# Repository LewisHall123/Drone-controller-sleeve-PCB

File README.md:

# Drone-controller-sleeve-PCB
A circuit designed to send commands to a drone that it controls. The inputs to the circuit that determine the commands come from six separate tribo-electric nanogenerators (TENG). The materials used for the TENG were aluminium foil and fluorinated ethylene propylene (FEP). The aluminium foil was arranged as six squares that sat on a sleeve that was secured to the users forearm. The aluminium squares were connected to electrodes that were inputs to the circuit. A glove was used with FEP material on the fingertips, and so when the user touched the aluminium squares on the sleeve, a voltage was created in the aluminium squares.
The six aluminium squares were controlls that were responsible for increasing or decreasing the values of roll, pitch, and yaw of the drone.
A Raspberry Pi Pico was used to determine the exact messages that could be sent to the HC-12 transceiver that would transmitt the commands to the drone.

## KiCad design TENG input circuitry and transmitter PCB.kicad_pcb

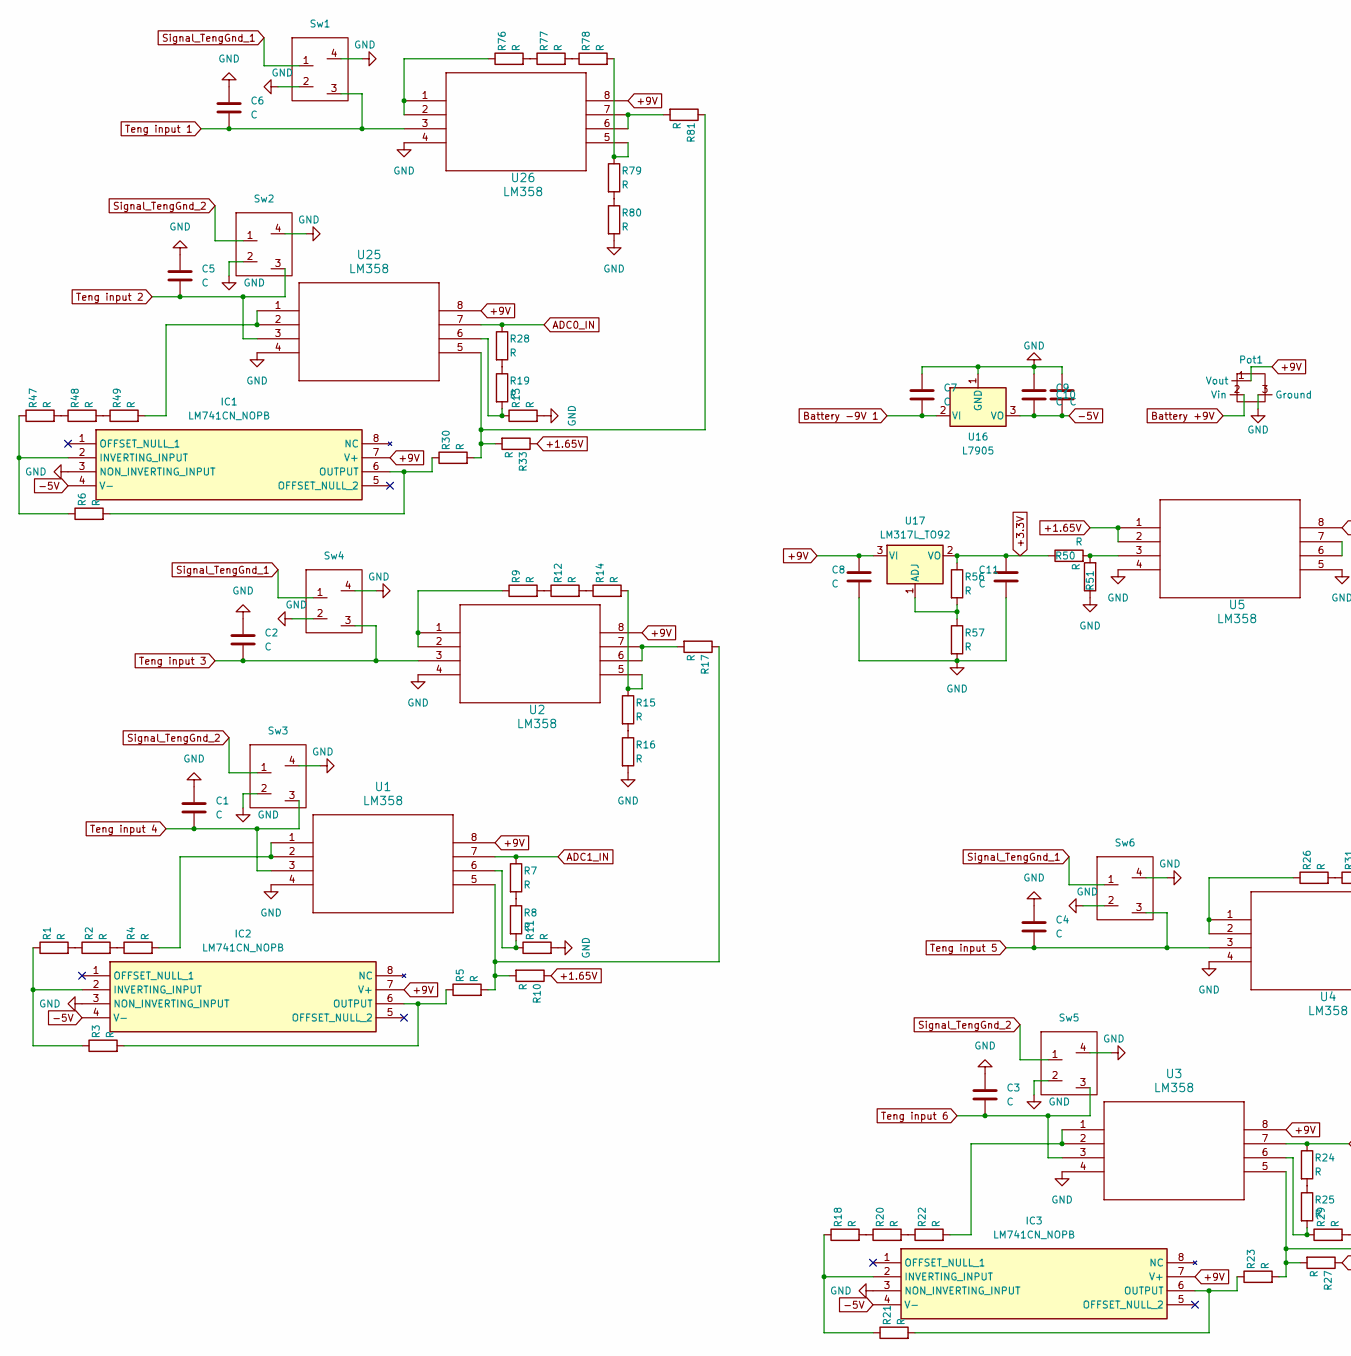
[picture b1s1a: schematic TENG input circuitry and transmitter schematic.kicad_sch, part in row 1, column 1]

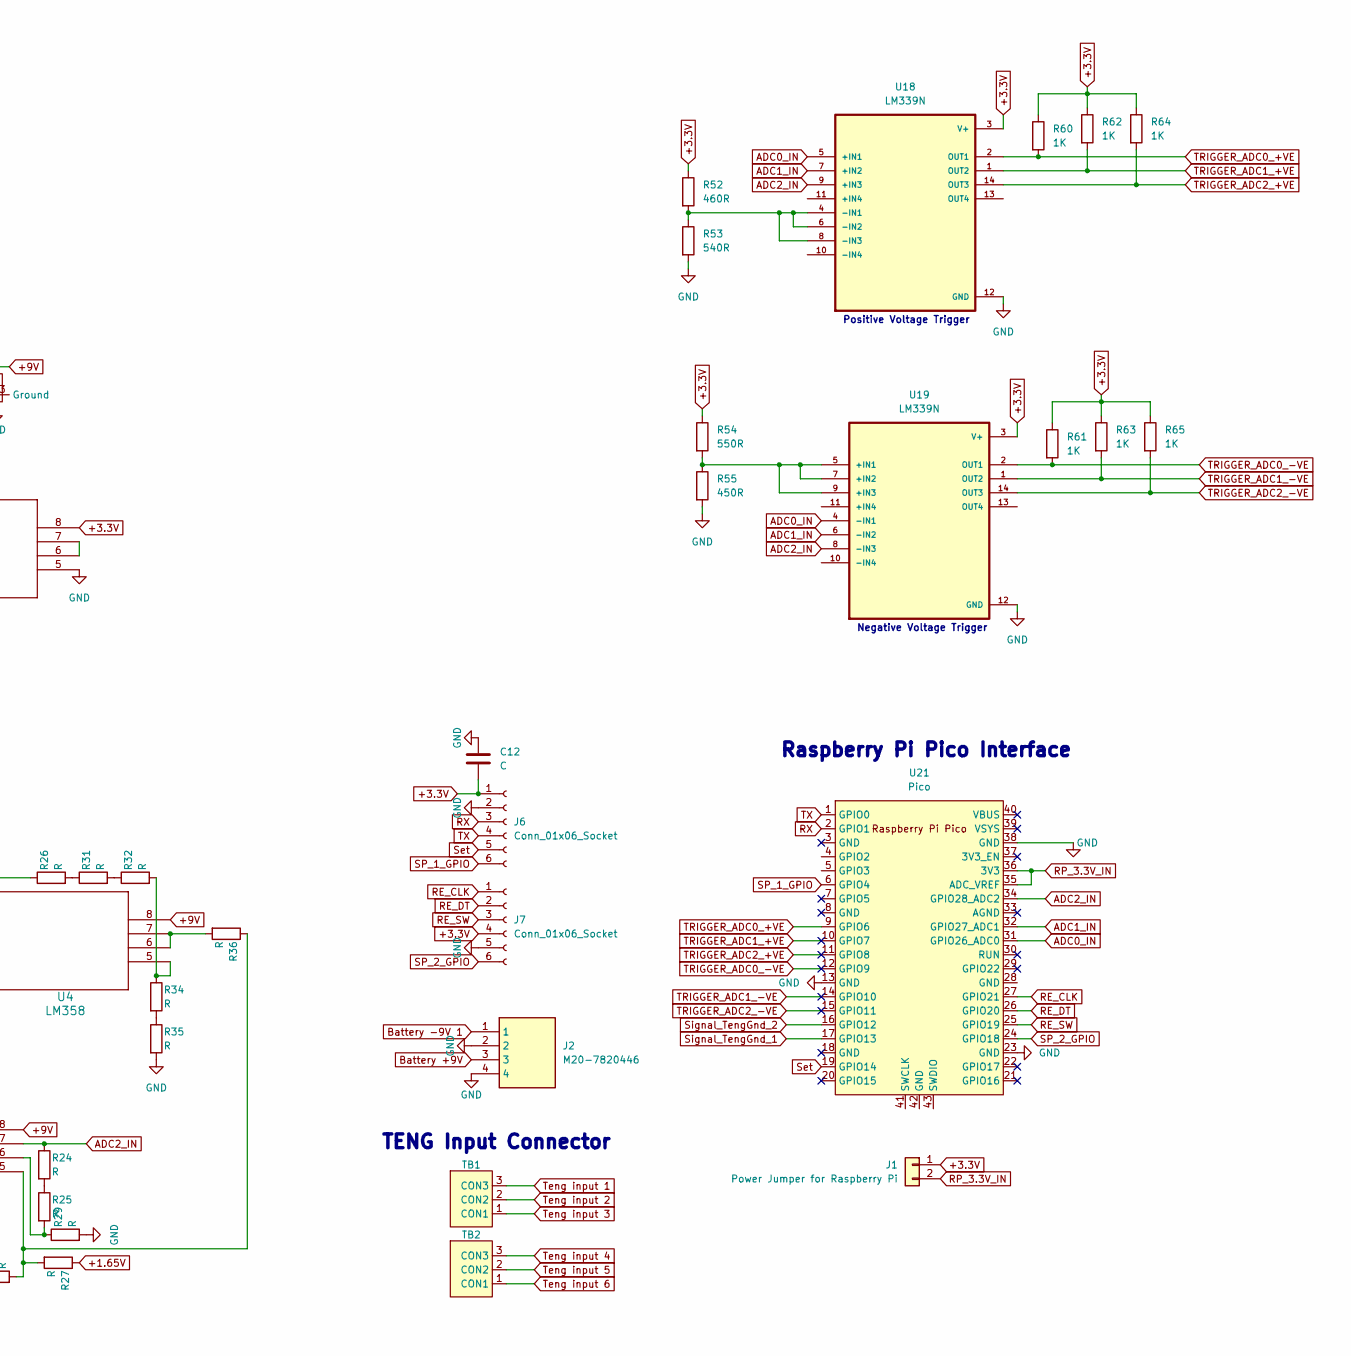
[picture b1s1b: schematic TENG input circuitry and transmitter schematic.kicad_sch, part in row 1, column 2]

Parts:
C1, C2, C3, C4, C5, C6: C; CP_Axial_L10.0mm_D6.0mm_P15.00mm_Horizontal
C7, C9, C10, C11, C12: C; C_Axial_L3.8mm_D2.6mm_P7.50mm_Horizontal
C8: C; CP_Radial_D8.0mm_P5.00mm
IC1, IC2, IC3: LM741CN_NOPB; DIP794W53P254L959H508Q8N; Mouser Part Number 926-LM741CN/NOPB
J1: Power Jumper for Raspberry Pi; PinHeader_1x02_P2.54mm_Vertical
J2: M20-7820446; RHDR4W70P0X254_1X4_1056X250X865P; Mouser Part Number 855-M20-7820446
J6, J7: Conn_01x06_Socket; PinSocket_1x06_P2.54mm_Vertical
Pot1: 3359V-A05
R1, R2, R3, R4, R5, R6, R7, R8, R9, R10, R11, R12, R13, R14, R15, R16, R17, R18, R19, R20, R21, R22, R23, R24, R25, R26, R27, R28, R29, R30, R31, R32, R33, R34, R35, R36, R47, R48, R49, R50, R51, R56, R57, R76, R77, R78, R79, R80, R81: R; R_Axial_DIN0207_L6.3mm_D2.5mm_P10.16mm_Horizontal
R52: 460R; R_Axial_DIN0207_L6.3mm_D2.5mm_P10.16mm_Horizontal
R53: 540R; R_Axial_DIN0207_L6.3mm_D2.5mm_P10.16mm_Horizontal
R54: 550R; R_Axial_DIN0207_L6.3mm_D2.5mm_P10.16mm_Horizontal
R55: 450R; R_Axial_DIN0207_L6.3mm_D2.5mm_P10.16mm_Horizontal
R60, R61, R62, R63, R64, R65: 1K; R_Axial_DIN0207_L6.3mm_D2.5mm_P10.16mm_Horizontal
Sw1, Sw2, Sw3, Sw4, Sw5, Sw6: RS 291-9675
TB1, TB2: CTB30513BK
U1, U2, U3, U4, U5, U25, U26: LM358; DIP8_300
U16: L7905; LM336BLPE325
U17: LM317L_TO92; LM336BLPE325
U18, U19: LM339N; LM339
U21: Pico; New Pico

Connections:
+1.65V: R10.1, R27.1, R33.1, U5.1, U5.2
+3.3V: C11.1, C12.2, J1.1, J6.1, J7.4, R50.1, R52.1, R54.1, R56.1, R60.1, R61.1, R62.1, R63.1, R64.1, R65.1, U5.8, U17.2 (VO), U18.3 (V+), U19.3 (V+)
+9V: C8.1, IC1.7 (V+), IC2.7 (V+), IC3.7 (V+), Pot1.1 (Vout), U1.8, U2.8, U3.8, U4.8, U17.3 (VI), U25.8, U26.8
-5V: C9.2, C10.2, IC1.4 (V-), IC2.4 (V-), IC3.4 (V-), U16.3 (VO)
ADC0_IN: R28.1, U18.5 (+IN1), U19.4 (-IN1), U21.31 (GPIO26_ADC0), U25.7
ADC1_IN: R7.1, U1.7, U18.7 (+IN2), U19.6 (-IN2), U21.32 (GPIO27_ADC1)
ADC2_IN: R24.1, U3.7, U18.9 (+IN3), U19.8 (-IN3), U21.34 (GPIO28_ADC2)
Battery +9V: J2.3, Pot1.2 (Vin)
Battery -9V 1: C7.2, J2.1, U16.2 (VI)
GND: C1.1, C2.1, C3.1, C4.1, C5.1, C6.1, C7.1, C8.2, C9.1, C10.1, C11.2, C12.1, IC1.3 (NON_INVERTING_INPUT), IC2.3 (NON_INVERTING_INPUT), IC3.3 (NON_INVERTING_INPUT), J2.2, J2.4, J6.2, J7.5, Pot1.3 (Ground), R11.2, R13.2, R16.2, R29.2, R35.2, R51.1, R53.2, R55.2, R57.2, R80.2, Sw1.2, Sw1.4, Sw2.2, Sw2.4, Sw3.2, Sw3.4, Sw4.2, Sw4.4, Sw5.2, Sw5.4, Sw6.2, Sw6.4, U1.4, U2.4, U3.4, U4.4, U5.4, U5.5, U16.1 (GND), U18.12 (GND), U19.12 (GND), U21.13 (GND), U21.23 (GND), U21.38 (GND), U25.4, U26.4
unnamed: IC1.2 (INVERTING_INPUT), R6.1, R47.1
unnamed: IC1.6 (OUTPUT), R6.2, R30.1
unnamed: IC2.2 (INVERTING_INPUT), R1.1, R3.1
unnamed: IC2.6 (OUTPUT), R3.2, R5.1
unnamed: IC3.2 (INVERTING_INPUT), R18.1, R21.1
unnamed: IC3.6 (OUTPUT), R21.2, R23.1
unnamed: R1.2, R2.1
unnamed: R2.2, R4.1
unnamed: R4.2, U1.1, U1.2
unnamed: R7.2, R8.1
unnamed: R9.1, U2.1, U2.2
unnamed: R5.2, R10.2, R17.1, U1.5
unnamed: R8.2, R11.1, U1.6
unnamed: R9.2, R12.1
unnamed: R12.2, R14.1
unnamed: R13.1, R19.2, U25.6
unnamed: R14.2, R15.1, U2.5
unnamed: R15.2, R16.1
unnamed: R17.2, U2.6, U2.7
unnamed: R18.2, R20.1
unnamed: R19.1, R28.2
unnamed: R20.2, R22.1
unnamed: R22.2, U3.1, U3.2
unnamed: R23.2, R27.2, R36.1, U3.5
unnamed: R24.2, R25.1
unnamed: R25.2, R29.1, U3.6
unnamed: R26.1, U4.1, U4.2
unnamed: R26.2, R31.1
unnamed: R30.2, R33.2, R81.1, U25.5
unnamed: R31.2, R32.1
unnamed: R32.2, R34.1, U4.5
unnamed: R34.2, R35.1
unnamed: R36.2, U4.6, U4.7
unnamed: R47.2, R48.1
unnamed: R48.2, R49.1
unnamed: R49.2, U25.1, U25.2
unnamed: R50.2, R51.2, U5.3
unnamed: R76.1, U26.1, U26.2
unnamed: R76.2, R77.1
unnamed: R77.2, R78.1
unnamed: R78.2, R79.1, U26.5
unnamed: R79.2, R80.1
unnamed: R81.2, U26.6, U26.7
unnamed: U5.6, U5.7
unnamed: R56.2, R57.1, U17.1 (ADJ)
unnamed: R52.2, R53.1, U18.4 (-IN1), U18.6 (-IN2), U18.8 (-IN3)
unnamed: R54.2, R55.1, U19.5 (+IN1), U19.7 (+IN2), U19.9 (+IN3)
RE_CLK: J7.1, U21.27 (GPIO21)
RE_DT: J7.2, U21.26 (GPIO20)
RE_SW: J7.3, U21.25 (GPIO19)
RP_3.3V_IN: J1.2, U21.35 (ADC_VREF), U21.36 (3V3)
RX: J6.3, U21.2 (GPIO1)
SP_1_GPIO: J6.6, U21.6 (GPIO4)
SP_2_GPIO: J7.6, U21.24 (GPIO18)
Set: J6.5, U21.19 (GPIO14)
Signal_TengGnd_1: Sw1.1, Sw4.1, Sw6.1, U21.17 (GPIO13)
Signal_TengGnd_2: Sw2.1, Sw3.1, Sw5.1, U21.16 (GPIO12)
TRIGGER_ADC0_+VE: R60.2, U18.2 (OUT1), U21.9 (GPIO6)
TRIGGER_ADC0_-VE: R61.2, U19.2 (OUT1), U21.12 (GPIO9)
TRIGGER_ADC1_+VE: R62.2, U18.1 (OUT2), U21.10 (GPIO7)
TRIGGER_ADC1_-VE: R63.2, U19.1 (OUT2), U21.14 (GPIO10)
TRIGGER_ADC2_+VE: R64.2, U18.14 (OUT3), U21.11 (GPIO8)
TRIGGER_ADC2_-VE: R65.2, U19.14 (OUT3), U21.15 (GPIO11)
TX: J6.4, U21.1 (GPIO0)
Teng input 1: C6.2, Sw1.3, TB1.3 (CON3), U26.3
Teng input 2: C5.2, Sw2.3, TB1.2 (CON2), U25.3
Teng input 3: C2.2, Sw4.3, TB1.1 (CON1), U2.3
Teng input 4: C1.2, Sw3.3, TB2.3 (CON3), U1.3
Teng input 5: C4.2, Sw6.3, TB2.2 (CON2), U4.3
Teng input 6: C3.2, Sw5.3, TB2.1 (CON1), U3.3

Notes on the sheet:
Raspberry Pi Pico Interface
Negative Voltage Trigger
Positive Voltage Trigger
TENG Input Connector

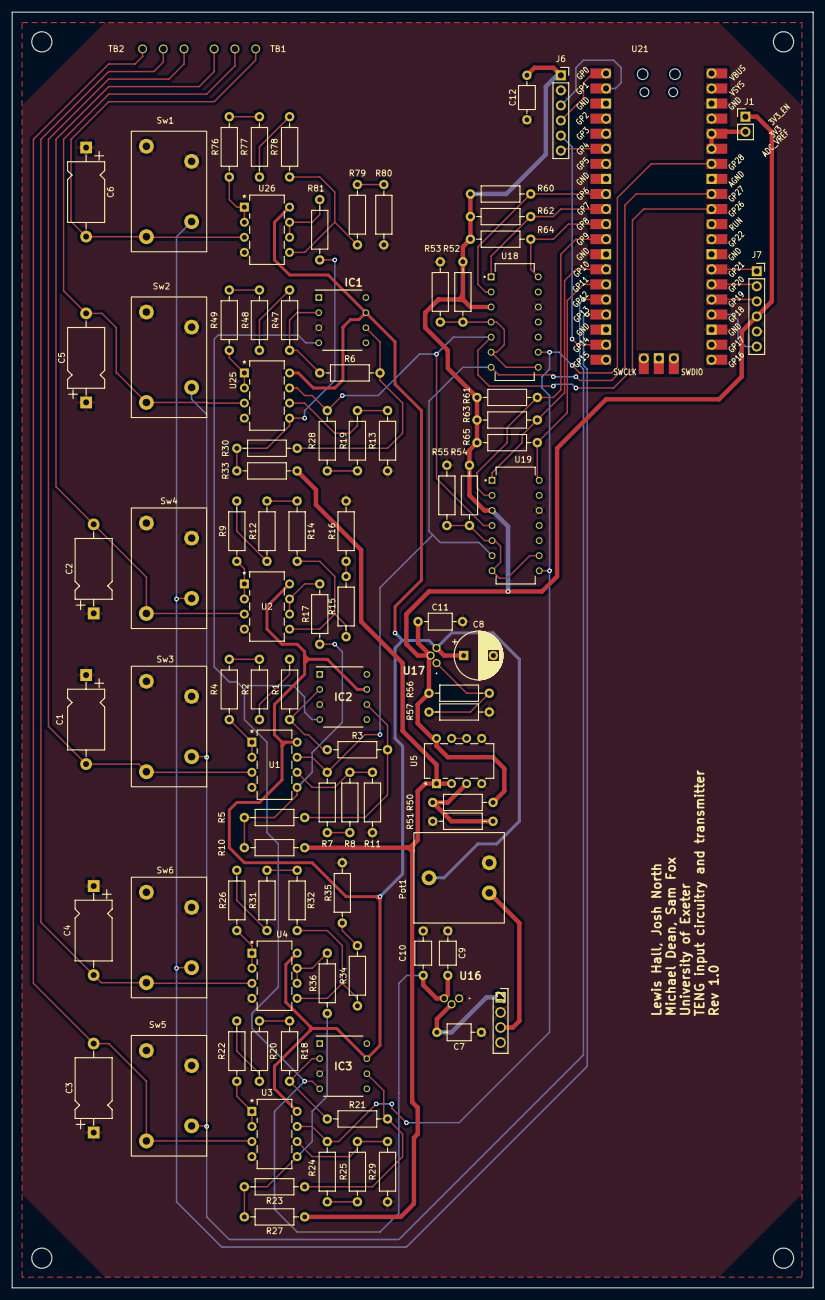
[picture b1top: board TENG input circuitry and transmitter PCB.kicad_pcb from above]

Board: 2 copper layers, 134.9 x 214.9 mm, 99 parts (0 on the bottom side), 80 nets.

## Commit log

2025-11-13 Upload of PCD layout, schematic, and Gerber files
2025-11-13 Enhance README with detailed project description
    Expanded the project description to include details about the materials used, the setup, and the components involved in the circuit.
2025-11-13 Picture of the finished PCB
2025-11-13 Rename project title in README
    Updated project title in README for clarity.
